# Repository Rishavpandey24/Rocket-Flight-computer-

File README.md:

# Rocket Flight Computer

A compact and reliable rocket flight computer designed for model and high-power rocketry. This system integrates an ESP32 microcontroller with sensors such as BMP280 (barometric pressure), MPU6050 (IMU), and GPS for real-time flight monitoring.

## Features

* Real-time altitude measurement
* Acceleration and orientation tracking
* Apogee detection
* Data logging to onboard storage
* Telemetry over Wi-Fi/LoRa
* Recovery system deployment support
* Flight data visualization and analysis

## Hardware

* ESP32
* BMP280 Barometric Sensor
* MPU6050 IMU
* GPS Module
* Buzzer and Status LEDs
* Battery Management System

## Applications

* Amateur and educational rocketry
* Flight testing and validation
* Aerospace research projects
* Rocket recovery and tracking

This project aims to provide a low-cost, customizable, and open-source avionics platform for rocket enthusiasts and students.

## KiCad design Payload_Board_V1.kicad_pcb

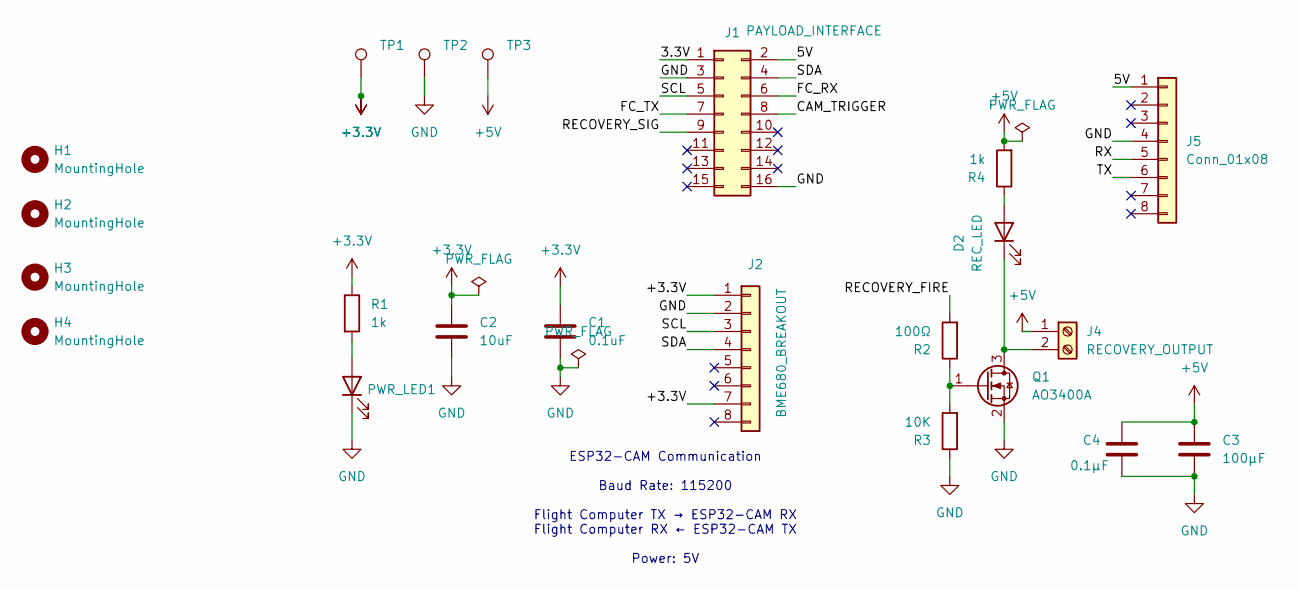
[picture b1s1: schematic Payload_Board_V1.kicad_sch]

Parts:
C1: 0.1uF; C_1206_3216Metric
C2: 10uF; C_1206_3216Metric
C3: 100µF; C_1210_3225Metric
C4: 0.1µF; C_1206_3216Metric
D2: REC_LED; LED_1206_3216Metric
H1, H2, H3, H4: MountingHole; MountingHole_3.2mm_M3
J1: PAYLOAD_INTERFACE; PinHeader_2x08_P2.54mm_Vertical
J2: BME680_BREAKOUT; Molex_KK-254_AE-6410-04A_1x04_P2.54mm_Vertical
J4: RECOVERY_OUTPUT; JST_XH_B2B-XH-A_1x02_P2.50mm_Vertical
J5: Conn_01x08; PinSocket_1x08_P2.54mm_Vertical
PWR_LED1: LED; LED_1206_3216Metric
Q1: AO3400A; SOT-23
R1, R4: 1k; R_1206_3216Metric
R2: 100Ω; R_1206_3216Metric
R3: 10K; R_1206_3216Metric
TP1, TP2, TP3: TestPoint; TestPoint_Pad_D2.0mm

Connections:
+3.3V: C1.1, C2.1, J2.1, J2.7, R1.1, TP1.1 (1_1)
+5V: C3.1, C4.1, J4.1, R4.2, TP3.1 (1_1)
/3.3V: J1.1
/5V: J1.2, J5.1
/CAM_TRIGGER: J1.8
/FC_RX: J1.6
/FC_TX: J1.7
/RECOVERY_FIRE: R2.2
/RECOVERY_SIG: J1.9
/RX: J5.5
/SCL: J1.5, J2.3
/SDA: J1.4, J2.4
/TX: J5.6
GND: C1.2, C2.2, C3.2, C4.2, J1.3, J1.16, J2.2, J5.4, PWR_LED1.1 (K), Q1.2 (S), R3.1, TP2.1 (1_1)
unnamed: D2.2 (A), R4.1
unnamed: D2.1 (K), J4.2, Q1.3 (D)
unnamed: PWR_LED1.2 (A), R1.2
unnamed: Q1.1 (G), R2.1, R3.2

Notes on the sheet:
ESP32-CAM Communication Baud Rate: 115200 Flight Computer TX → ESP32-CAM RX Flight Computer RX ← ESP32-CAM TX Power: 5V

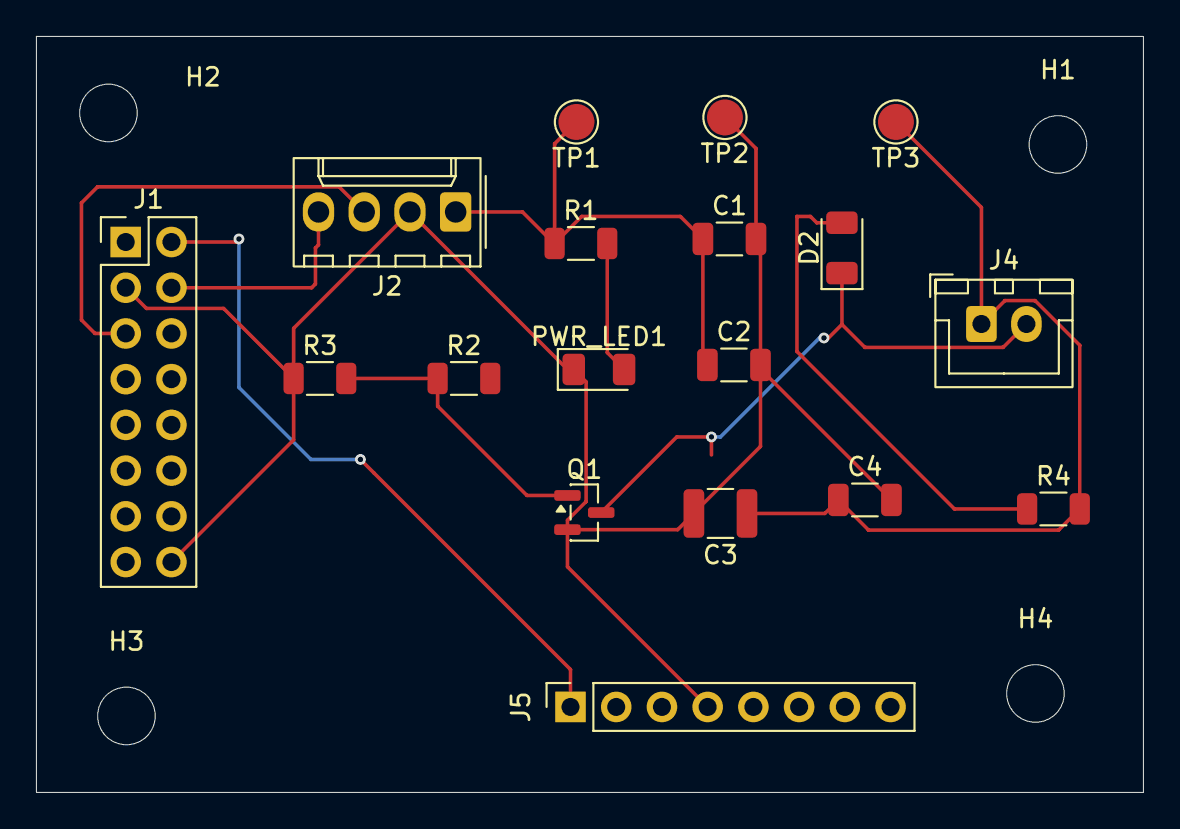
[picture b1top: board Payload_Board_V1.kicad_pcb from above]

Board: 2 copper layers, 61.5 x 42.0 mm, 22 parts (0 on the bottom side), 10 nets.

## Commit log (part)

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2026-05-29 Add altimeter and merge system
2026-05-29 Remove unwanted files
2026-05-29 Remove unwanted files from GitHub
